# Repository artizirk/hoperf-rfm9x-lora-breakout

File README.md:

# hoperf-rfm9x-lora-breakout
This is a simple breakout board for HopeRF LoRa RFM95/96/97/98W Transceiver.

you could either put SMA or uFL connectors on this board or just simply solder a wire or helical antenna directly.

This project is converted from [Eagle project](https://github.com/altro-id/hoperf-rfm9x-lora-breakout) to KiCad 5.1

## Product Preview and Configurations

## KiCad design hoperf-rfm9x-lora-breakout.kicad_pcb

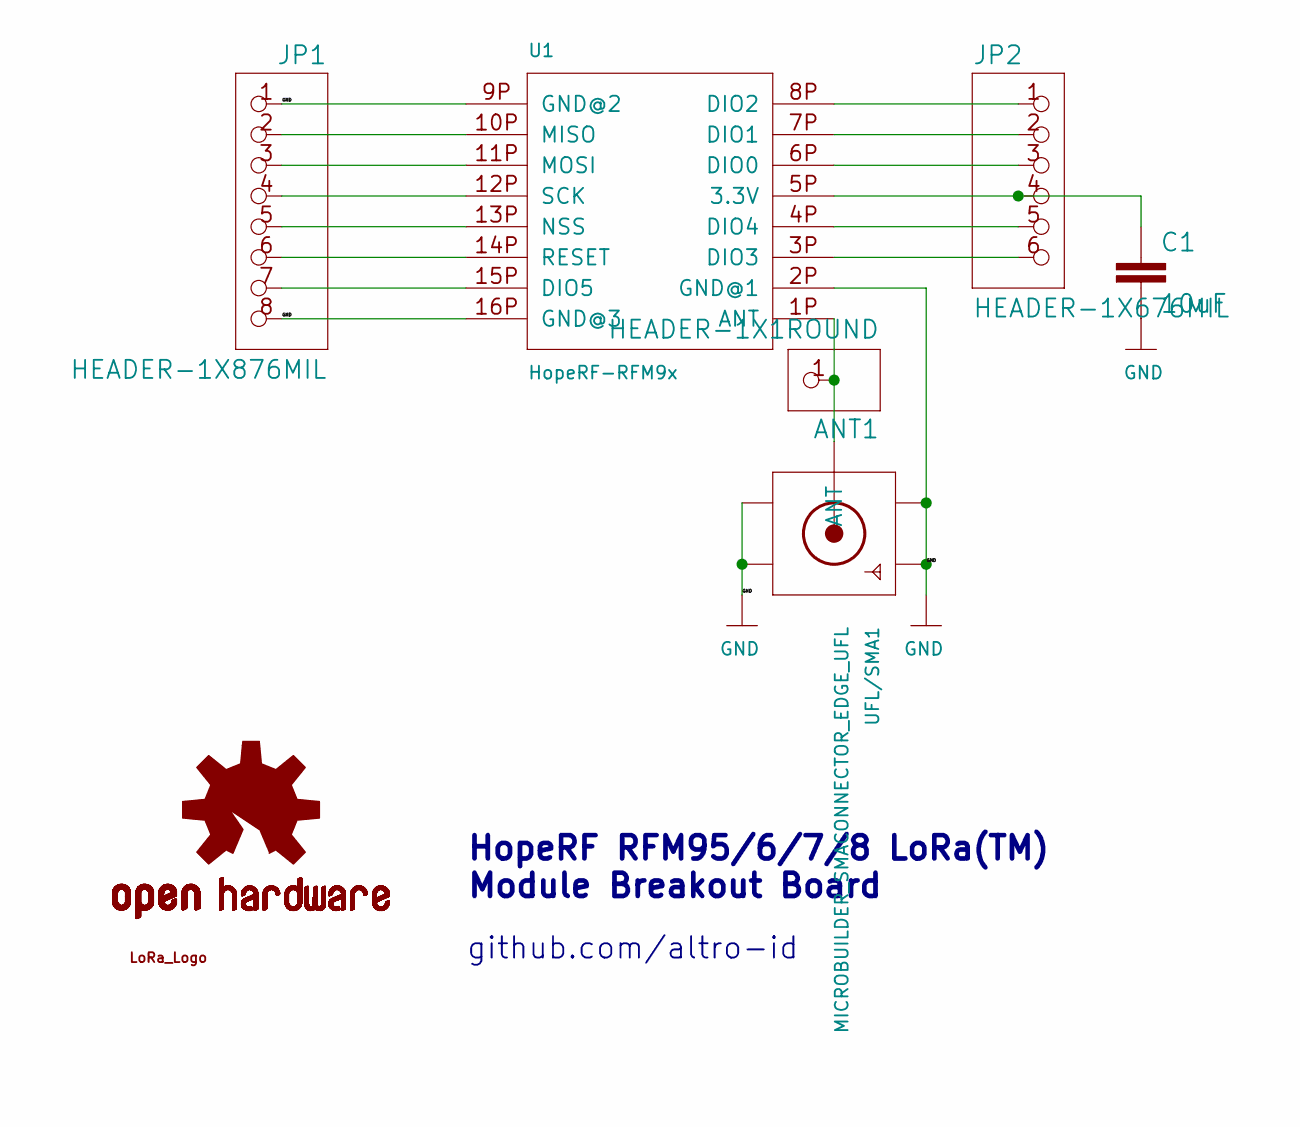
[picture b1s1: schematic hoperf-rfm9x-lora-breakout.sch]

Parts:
ANT1: HEADER-1X1ROUND; 1X01_ROUND
C1: 10uF; 0805_MP
JP1: HEADER-1X876MIL; 1X08_ROUND_76
JP2: HEADER-1X676MIL; 1X06_ROUND_76
LOGO1: OSHW-LOGOS; OSHW-LOGO-S
U1: HopeRF-RFM9x; RFM9X_SMT
U$3: LORA_LOGO
UFL/SMA1: MICROBUILDER_SMACONNECTOR_EDGE_UFL; MICROBUILDER_SMA_EDGELAUNCH_UFL

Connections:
GND: C1.2, JP1.1, JP1.8, U1.2P (GND@1), U1.9P (GND@2), U1.16P (GND@3), UFL/SMA1.GND@1 (GND1), UFL/SMA1.GND@2 (GND2), UFL/SMA1.GND@3 (GND3), UFL/SMA1.GND@4 (GND4)
unnamed: ANT1.1, U1.1P (ANT), UFL/SMA1.P (ANT)
unnamed: C1.1, JP2.4, U1.5P (3.3V)
unnamed: JP1.2, U1.10P (MISO)
unnamed: JP1.3, U1.11P (MOSI)
unnamed: JP1.4, U1.12P (SCK)
unnamed: JP1.5, U1.13P (NSS)
unnamed: JP1.6, U1.14P (RESET)
unnamed: JP1.7, U1.15P (DIO5)
unnamed: JP2.1, U1.8P (DIO2)
unnamed: JP2.2, U1.7P (DIO1)
unnamed: JP2.3, U1.6P (DIO0)
unnamed: JP2.5, U1.4P (DIO4)
unnamed: JP2.6, U1.3P (DIO3)

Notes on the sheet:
HopeRF RFM95/6/7/8 LoRa(TM) Module Breakout Board
github.com/altro-id

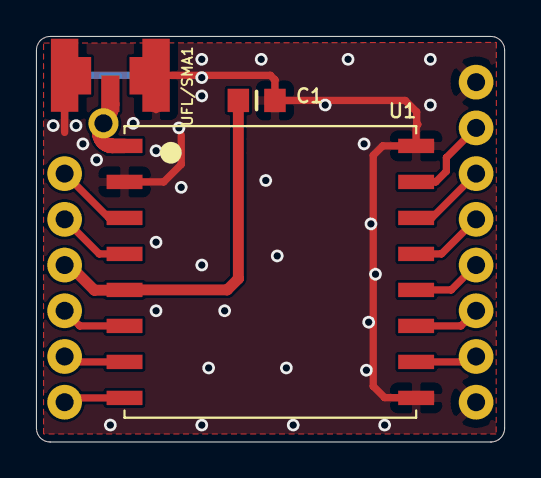
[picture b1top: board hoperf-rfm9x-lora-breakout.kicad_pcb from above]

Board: 2 copper layers, 26.0 x 22.5 mm, 8 parts (0 on the bottom side), 14 nets.

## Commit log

2021-07-26 Add KiCad version
